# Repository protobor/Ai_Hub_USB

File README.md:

fe1.1s hub
==========

cloned from https://github.com/acrobotic/Ai_Hub_USB

Fork
----

 * completely redesigned
 * added support for gang power control (tested, ok)
 * will correctly switch between bus power and external power (self powered signal is inverted)

Issues
------

 * MOSFET footprint is fu...., so to assembly you'll need to bend legs and solder it upside down;
 * Something wrong with milling for usb micro b connector;
 * Bus powered and self powered signals inverted.

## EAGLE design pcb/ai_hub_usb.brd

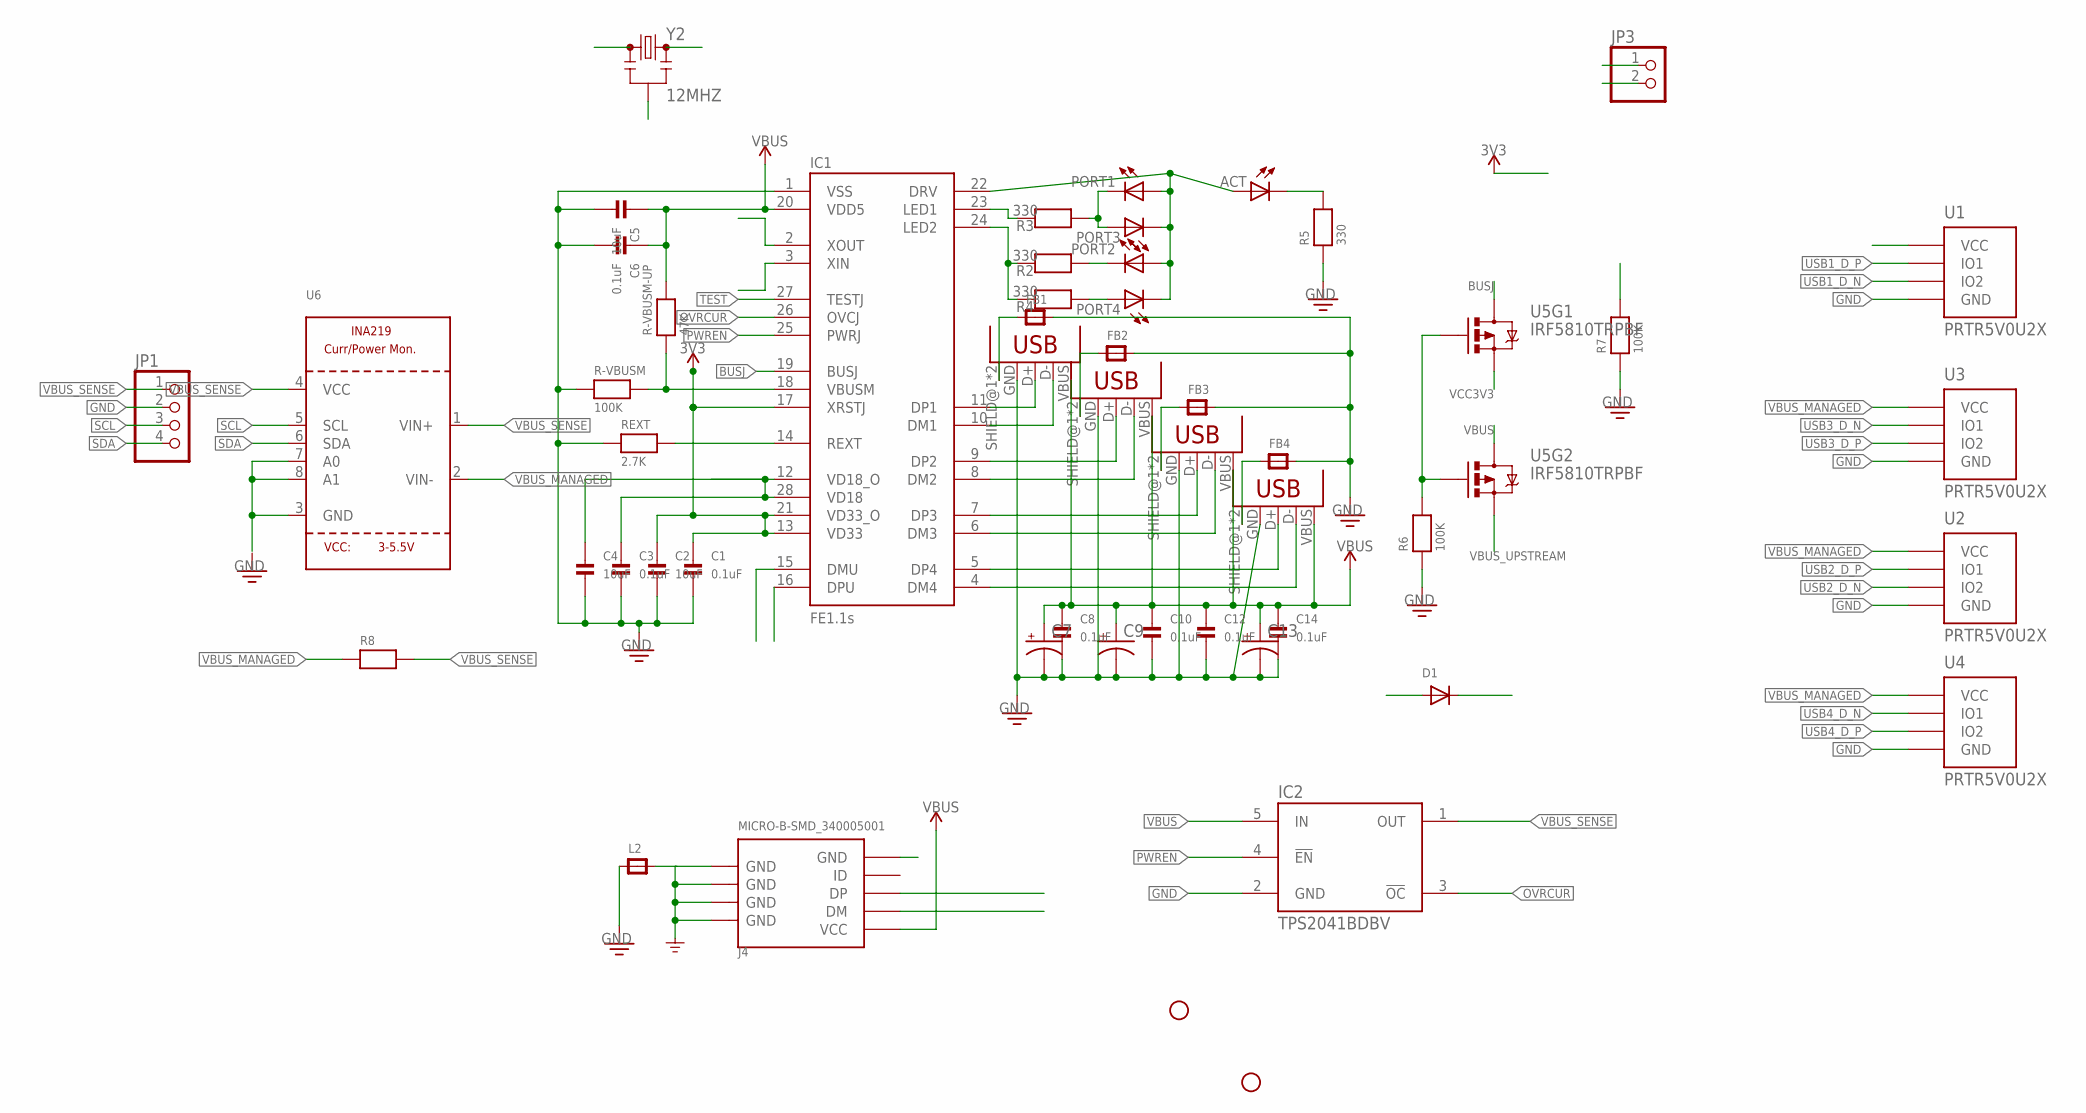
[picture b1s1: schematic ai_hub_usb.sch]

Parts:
ACT: LED0603; LED-0603
C1, C3, C6, C8, C10, C12, C14: 0.1uF; _0603MP
C2, C4, C5: 10uF; _0603MP
C7, C9, C13: CAP_POLD; PANASONIC_D
D1: DIODESMA; SMADIODE
FB1, FB2, FB3, FB4: FERRITE_0603MP; _0603MP
IC1: FE1.1S; FE1.1S_SSOP-28
IC2: TPS2041BDBV; SOT23-5L
J4: MICRO-B-SMD_340005001; MICRO-USB
JP1: HEADER-1X4ROUND; 1X04_ROUND
JP3: HEADER-1X2ROUND; 1X02_ROUND
L2: FERRITE_0603MP; _0603MP
PORT1, PORT2, PORT3, PORT4: LED0603; LED-0603
R2, R3, R4, R5: 330; _0603MP
R6, R7: 100K; _0603MP
R8: RESISTOR1206; 1206
R-VBUSM: 100K; _0603MP
R-VBUSM-UP: 47K; _0603MP
REXT: 2.7K; _0603MP
STANDOFF1, STANDOFF4: STAND-OFF4; STAND-OFF-4
U1, U2, U3, U4: PRTR5V0U2X; SOT-143B
U5: IRF5810TRPBF; SOT23-6
U6: INA219; SOT23-8
USB1, USB3, USB4: USBA-PTH-VERTICAL; USB-A-F-PTH-VERTICAL
USB2: USBA-PTH; USB-A-F-PTH
Y2: 12MHZ; RESONATOR-SMD

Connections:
BUSJ: IC1.19 (BUSJ), R7.2, U5.6 (D)
DRV: ACT.A, IC1.22 (DRV), PORT1.A, PORT2.A, PORT3.C, PORT4.C
GND: C1.2, C2.2, C3.2, C4.2, C5.2, C6.2, C7.-, C8.2, C9.-, C10.2, C12.2, C13.-, C14.2, FB1.2, FB2.2, FB3.2, FB4.2, IC1.1 (VSS), IC2.2 (GND), J4.5 (GND), JP1.2, JP3.2, L2.1, R5.1, R6.1, R7.1, R-VBUSM.1, REXT.1, U1.1 (GND), U2.1 (GND), U3.1 (GND), U4.1 (GND), U6.3 (GND), U6.7 (A0), U6.8 (A1), USB1.GND, USB2.GND, USB3.GND, USB4.GND, Y2.2
LED1: IC1.23 (LED1), R3.1
LED2: IC1.24 (LED2), R2.1, R4.1
unnamed: IC1.14 (REXT), REXT.2
unnamed: FB1.1, USB1.SHIELD@1 (SHIELD), USB1.SHIELD@2 (SHIELD)
unnamed: FB2.1, USB2.SHIELD@1 (SHIELD), USB2.SHIELD@2 (SHIELD)
unnamed: FB3.1, USB3.SHIELD@1 (SHIELD), USB3.SHIELD@2 (SHIELD)
unnamed: FB4.1, USB4.SHIELD@1 (SHIELD), USB4.SHIELD@2 (SHIELD)
unnamed: PORT2.C, R2.2
unnamed: PORT4.A, R4.2
unnamed: PORT1.C, PORT3.A, R3.2
unnamed: ACT.C, R5.2
OSC_IN: IC1.3 (XIN), Y2.1
OSC_OUT: IC1.2 (XOUT), Y2.3
OVRCUR: IC1.26 (OVCJ), IC2.3 (!OC)
PWREN: IC1.25 (PWRJ), IC2.4 (!EN)
SCL: JP1.3, U6.5 (SCL)
SDA: JP1.4, U6.6 (SDA)
TEST: IC1.27 (TESTJ)
USB1_D_N: IC1.10 (DM1), U1.3 (IO2), USB1.D-
USB1_D_P: IC1.11 (DP1), U1.2 (IO1), USB1.D+
USB2_D_N: IC1.8 (DM2), U2.3 (IO2), USB2.D-
USB2_D_P: IC1.9 (DP2), U2.2 (IO1), USB2.D+
USB3_D_N: IC1.6 (DM3), U3.2 (IO1), USB3.D-
USB3_D_P: IC1.7 (DP3), U3.3 (IO2), USB3.D+
USB4_D_N: IC1.4 (DM4), U4.2 (IO1), USB4.D-
USB4_D_P: IC1.5 (DP4), U4.3 (IO2), USB4.D+
USB_D_N: IC1.15 (DMU), J4.2 (DM)
USB_D_P: IC1.16 (DPU), J4.3 (DP)
USB_SHIELD: J4.S1 (GND), J4.S2 (GND), J4.S3 (GND), J4.S4 (GND), J4.S5 (GND), J4.S6 (GND), L2.2
VBUS: C5.1, C6.1, D1.C, IC1.20 (VDD5), IC2.5 (IN), R-VBUSM-UP.2, U5.4 (D)
VBUS_MANAGED: C7.+, C8.1, C9.+, C10.1, C12.1, C13.+, C14.1, R8.1, U1.4 (VCC), U2.4 (VCC), U3.4 (VCC), U4.4 (VCC), U6.2 (VIN-), USB1.VBUS, USB2.VBUS, USB3.VBUS, USB4.VBUS
VBUS_MONITOR: IC1.18 (VBUSM), R-VBUSM.2, R-VBUSM-UP.1
VBUS_SENSE: IC2.1 (OUT), JP1.1, R8.2, U6.1 (VIN+), U6.4 (VCC)
VBUS_UPSTREAM: J4.1 (VCC), U5.2 (S)
VCC1V8: C3.1, C4.1, IC1.12 (VD18_O), IC1.28 (VD18)
VCC3V3: C1.1, C2.1, IC1.13 (VD33), IC1.17 (XRSTJ), IC1.21 (VD33_O), U5.5 (S)
VEXT: D1.A, JP3.1, R6.2, U5.1 (G), U5.3 (G)

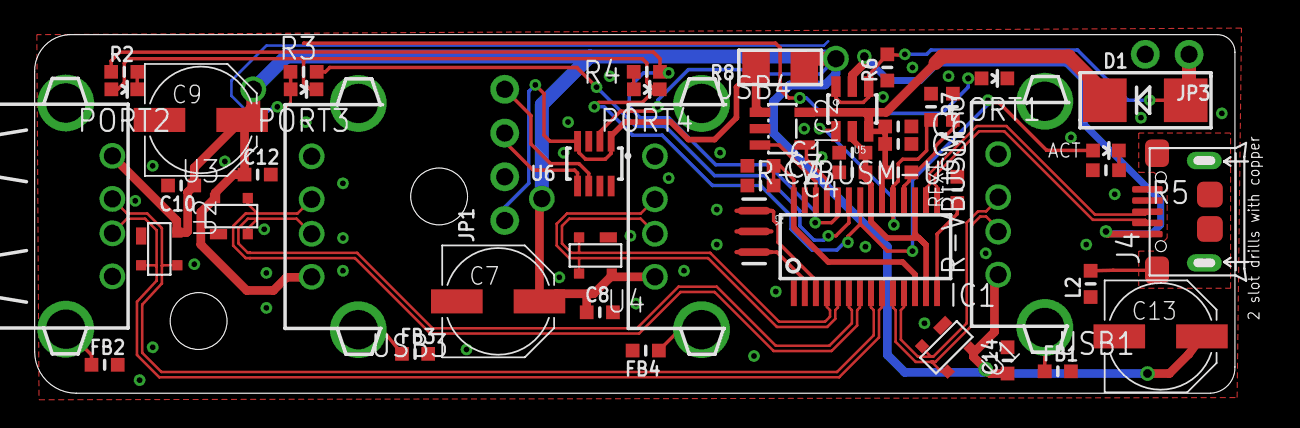
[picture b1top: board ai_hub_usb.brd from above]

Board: 2 copper layers, 71.0 x 20.3 mm, 52 parts (0 on the bottom side), 39 nets.

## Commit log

2017-08-15 redesign: gang power control, smaller layout
2017-08-24 docs: updated status

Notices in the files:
parts and their libraries:
microbuilder: This work is placed in the public domain, and may be freely used for commercial and non-commercial work with the following conditions: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
SparkFun-Passives: Licensing: Creative Commons ShareAlike 4.0 International - https://creativecommons.org/licenses/by-sa/4.0
